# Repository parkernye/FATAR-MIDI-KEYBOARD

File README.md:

# FATAR-MIDI-KEYBOARD
 Daughter board for fatar keybed.
 
[FATAR](http://www.fatar.com/) makes an extremely rugged 44-key keyboard with weighted keys. It is the most natural feeling key-bed that resembles an actual grand paino in a small footprint. 

The goal of this project is to use this keybed as a user interface a future modular synth. It follows the [midi protocol](https://en.wikipedia.org/wiki/MIDI) and then is HEAVILY influenced by [elkayem's midi2cv project](https://github.com/elkayem/midi2cv) to convert this midi signal to various control voltages. It is all ported onto a single PCB which connects directly to the prexisting fatar pcb.

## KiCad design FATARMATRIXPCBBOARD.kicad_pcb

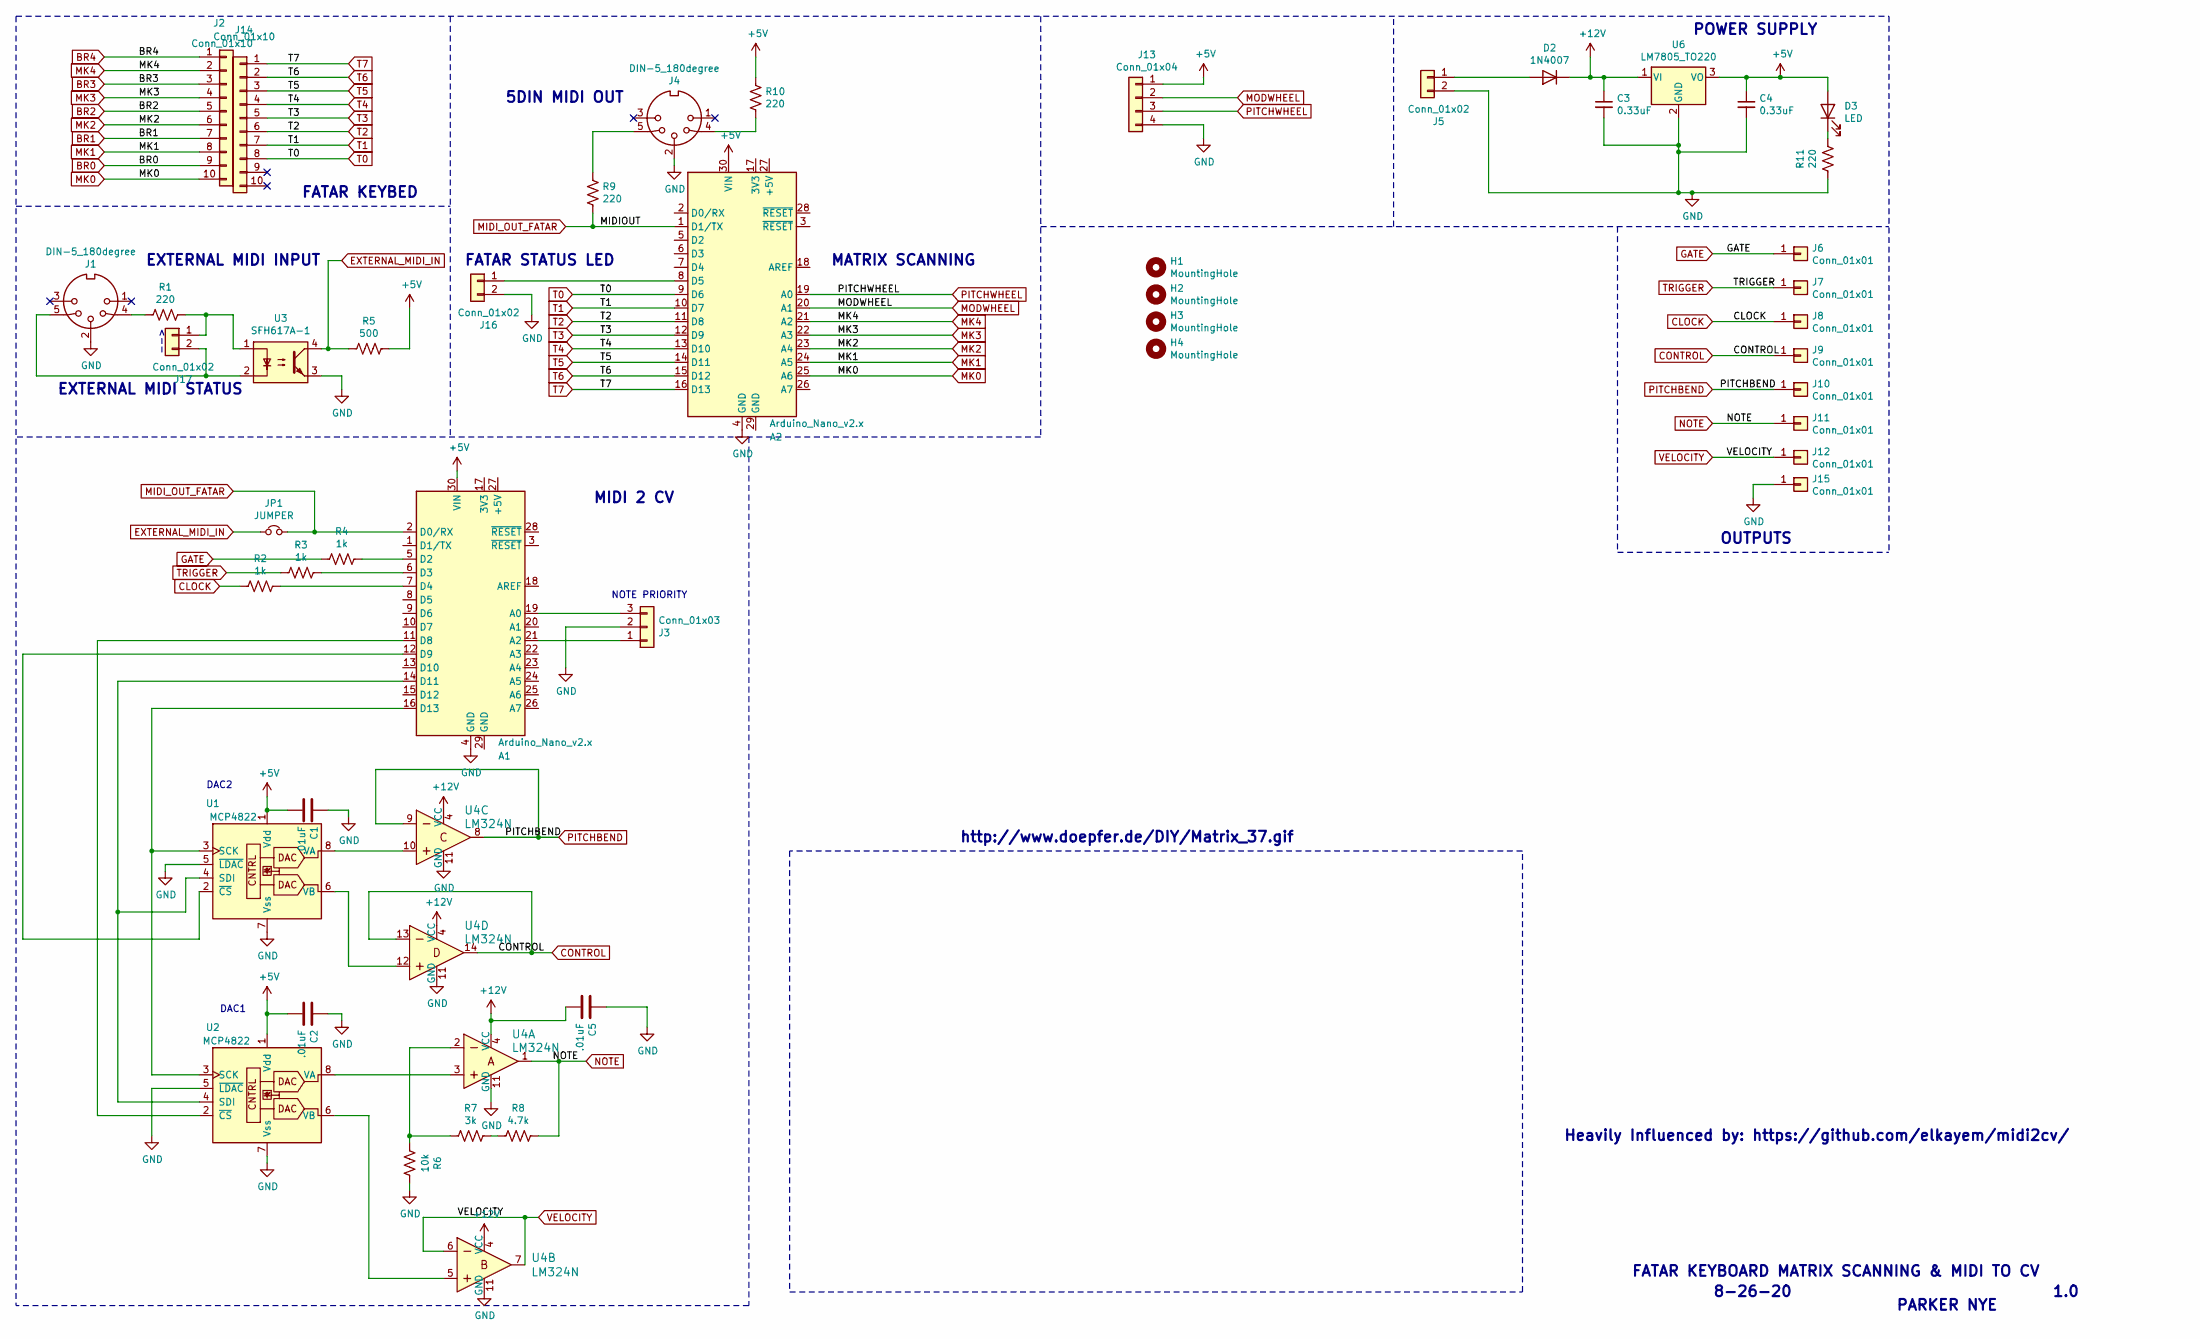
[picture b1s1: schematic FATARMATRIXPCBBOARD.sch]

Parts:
A1, A2: Arduino_Nano_v2.x; Arduino_Nano
C1, C2, C5: .01uF; C_Rect_L7.2mm_W2.5mm_P5.00mm_FKS2_FKP2_MKS2_MKP2
C3, C4: 0.33uF; C_Rect_L7.2mm_W2.5mm_P5.00mm_FKS2_FKP2_MKS2_MKP2
D2: 1N4007; D_DO-41_SOD81_P10.16mm_Horizontal
D3: LED; LED_D5.0mm
H1, H2, H3, H4: MountingHole; MountingHole_3mm
J1, J4: DIN-5_180degree; PinSocket_1x05_P2.54mm_Vertical
J2, J14: Conn_01x10; PinSocket_1x10_P2.54mm_Vertical
J3: Conn_01x03; PinSocket_1x03_P2.54mm_Vertical
J5, J16, J17: Conn_01x02; PinSocket_1x02_P2.54mm_Vertical
J6, J7, J8, J9, J10, J11, J12, J15: Conn_01x01; PinSocket_1x01_P2.54mm_Vertical
J13: Conn_01x04; PinSocket_1x04_P2.54mm_Vertical
JP1: JUMPER; SolderJumper-2_P1.3mm_Open_RoundedPad1.0x1.5mm
R1, R9, R10, R11: 220; R_Axial_DIN0207_L6.3mm_D2.5mm_P7.62mm_Horizontal
R2, R3, R4: 1k; R_Axial_DIN0207_L6.3mm_D2.5mm_P7.62mm_Horizontal
R5: 500; R_Axial_DIN0207_L6.3mm_D2.5mm_P7.62mm_Horizontal
R6: 10k; R_Axial_DIN0207_L6.3mm_D2.5mm_P7.62mm_Horizontal
R7: 3k; R_Axial_DIN0207_L6.3mm_D2.5mm_P7.62mm_Horizontal
R8: 4.7k; R_Axial_DIN0207_L6.3mm_D2.5mm_P7.62mm_Horizontal
U1, U2: MCP4822; DIP-8_W7.62mm_Socket_LongPads
U3: SFH617A-1; DIP-4_W7.62mm
U4: LM324N; DIP-14_W7.62mm_Socket_LongPads; MPN LM324N; Digi-Key_PN 296-1391-5-ND
U6: LM7805_TO220; TO-220-3_Vertical

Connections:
+5V: A1.30 (VIN), A2.30 (VIN), C1.2, C2.2, C4.1, D3.2 (A), J13.1, R5.2, R10.1, U1.1 (Vdd), U2.1 (Vdd), U6.3 (VO)
+12V: C3.1, C5.2, D2.1 (K), U4.4 (VCC), U6.1 (VI)
BR0: J2.9
BR1: J2.7
BR2: J2.5
BR3: J2.3
BR4: J2.1
CLOCK: J8.1, R2.1
CONTROL: J9.1, U4.13, U4.14
EXTERNAL_MIDI_IN: JP1.1, R5.1, U3.4
GATE: J6.1, R4.1
GND: A1.4 (GND), A2.4 (GND), C1.1, C2.1, C3.2, C4.2, C5.1, J1.2, J3.2, J4.2, J5.2, J13.4, J15.1, J16.2, R6.2, R11.1, U1.5 (~LDAC), U1.7 (Vss), U2.5 (~LDAC), U2.7 (Vss), U3.3, U4.11 (GND), U6.2 (GND)
MIDI_OUT_FATAR: A1.2 (D0/RX), A2.1 (D1/TX), JP1.2, R9.2
MK0: A2.25 (A6), J2.10
MK1: A2.24 (A5), J2.8
MK2: A2.23 (A4), J2.6
MK3: A2.22 (A3), J2.4
MK4: A2.21 (A2), J2.2
MODWHEEL: A2.20 (A1), J13.2
NOTE: J11.1, R8.2, U4.1
unnamed: A1.5 (D2), R4.2
unnamed: A1.6 (D3), R3.2
unnamed: A1.7 (D4), R2.2
unnamed: A1.11 (D8), U2.2 (~CS)
unnamed: A1.12 (D9), U1.2 (~CS)
unnamed: A1.14 (D11), U1.4 (SDI), U2.4 (SDI)
unnamed: A1.16 (D13), U1.3 (SCK), U2.3 (SCK)
unnamed: A1.19 (A0), J3.3
unnamed: A1.21 (A2), J3.1
unnamed: A2.8 (D5), J16.1
unnamed: D2.2 (A), J5.1
unnamed: D3.1 (K), R11.2
unnamed: J1.4, R1.1
unnamed: J1.5, J17.2, U3.2
unnamed: J4.4, R10.2
unnamed: J4.5, R9.1
unnamed: J17.1, R1.2, U3.1
unnamed: R6.1, R7.1, U4.2
unnamed: R7.2, R8.1
unnamed: U1.6 (VB), U4.12
unnamed: U1.8 (VA), U4.10
unnamed: U2.6 (VB), U4.5
unnamed: U2.8 (VA), U4.3
PITCHBEND: J10.1, U4.8, U4.9
PITCHWHEEL: A2.19 (A0), J13.3
T0: A2.9 (D6), J14.8
T1: A2.10 (D7), J14.7
T2: A2.11 (D8), J14.6
T3: A2.12 (D9), J14.5
T4: A2.13 (D10), J14.4
T5: A2.14 (D11), J14.3
T6: A2.15 (D12), J14.2
T7: A2.16 (D13), J14.1
TRIGGER: J7.1, R3.1
VELOCITY: J12.1, U4.6, U4.7

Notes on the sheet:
FATAR KEYBED
EXTERNAL MIDI INPUT
POWER SUPPLY
DAC1
NOTE PRIORITY
DAC2
MATRIX SCANNING
MIDI 2 CV
OUTPUTS
FATAR KEYBOARD MATRIX SCANNING & MIDI TO CV
8-26-20
1.0
PARKER NYE
Heavily Influenced by: https://github.com/elkayem/midi2cv/
http://www.doepfer.de/DIY/Matrix_37.gif
5DIN MIDI OUT
FATAR STATUS LED
EXTERNAL MIDI STATUS
-->

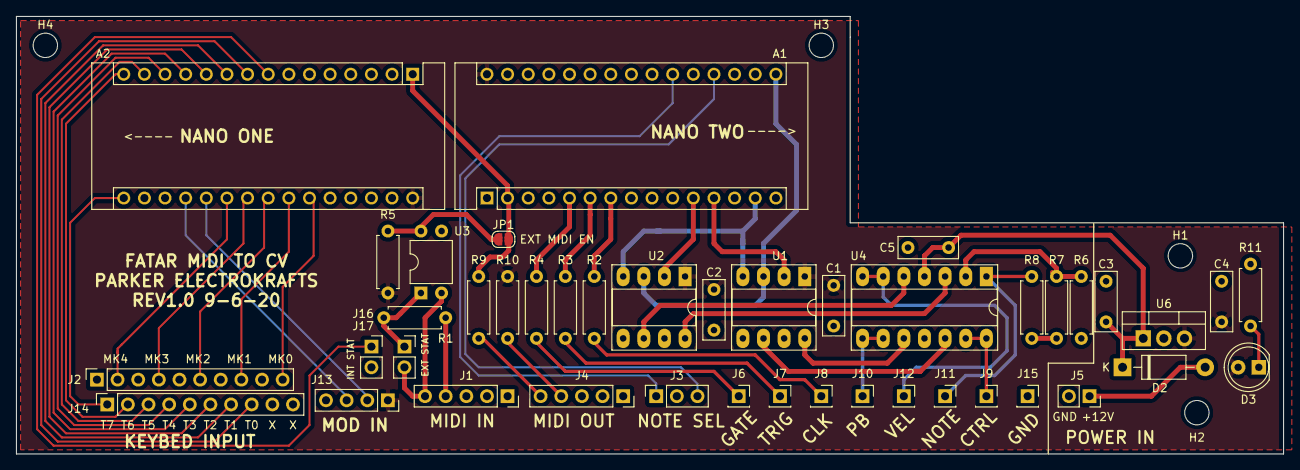
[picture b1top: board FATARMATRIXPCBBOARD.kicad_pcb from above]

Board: 2 copper layers, 156.0 x 53.8 mm, 47 parts (0 on the bottom side), 50 nets.

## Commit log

2020-09-18 init commit
2020-09-18 added pictures
2020-09-27 added picture
